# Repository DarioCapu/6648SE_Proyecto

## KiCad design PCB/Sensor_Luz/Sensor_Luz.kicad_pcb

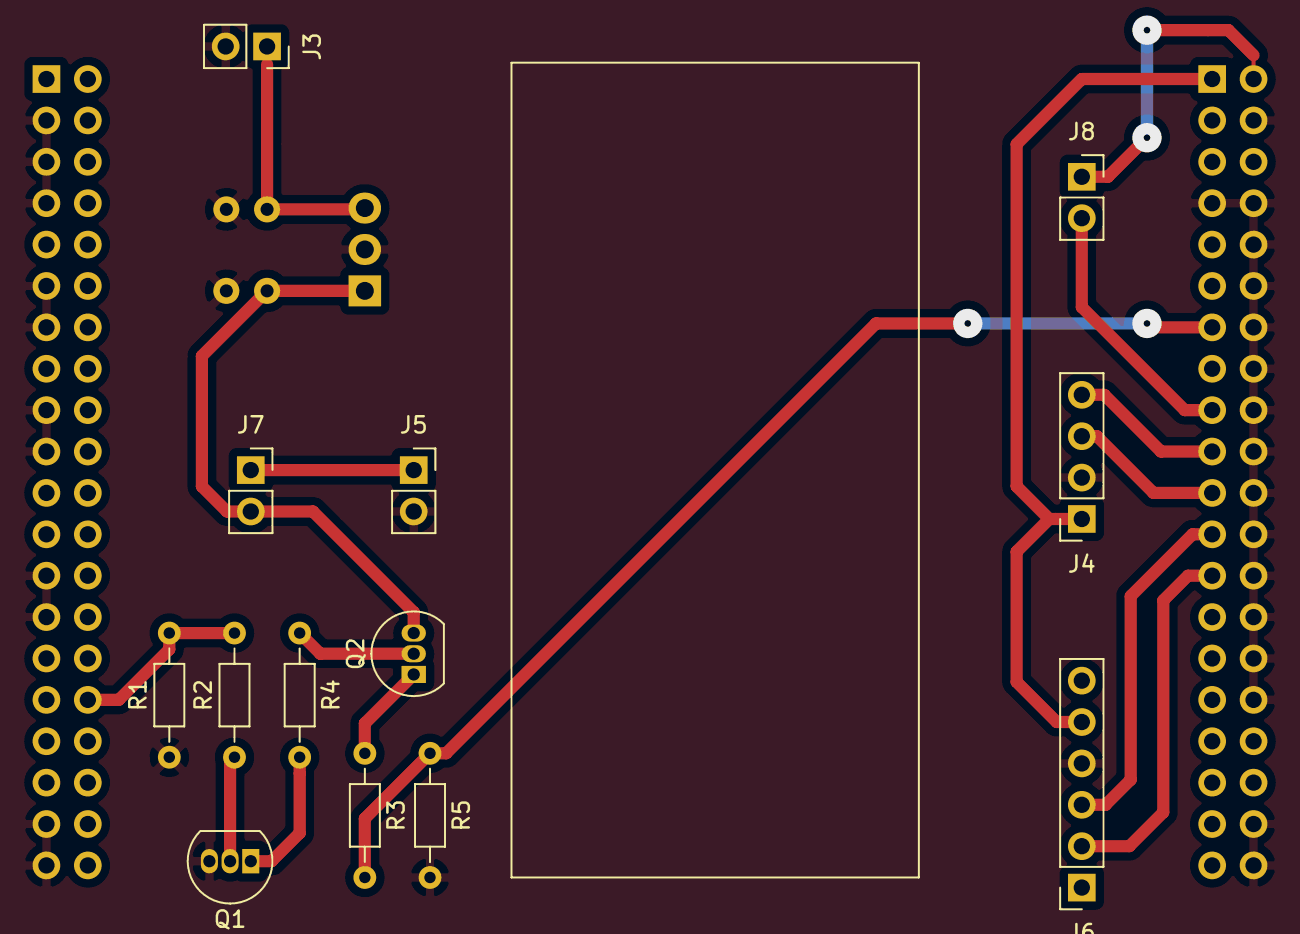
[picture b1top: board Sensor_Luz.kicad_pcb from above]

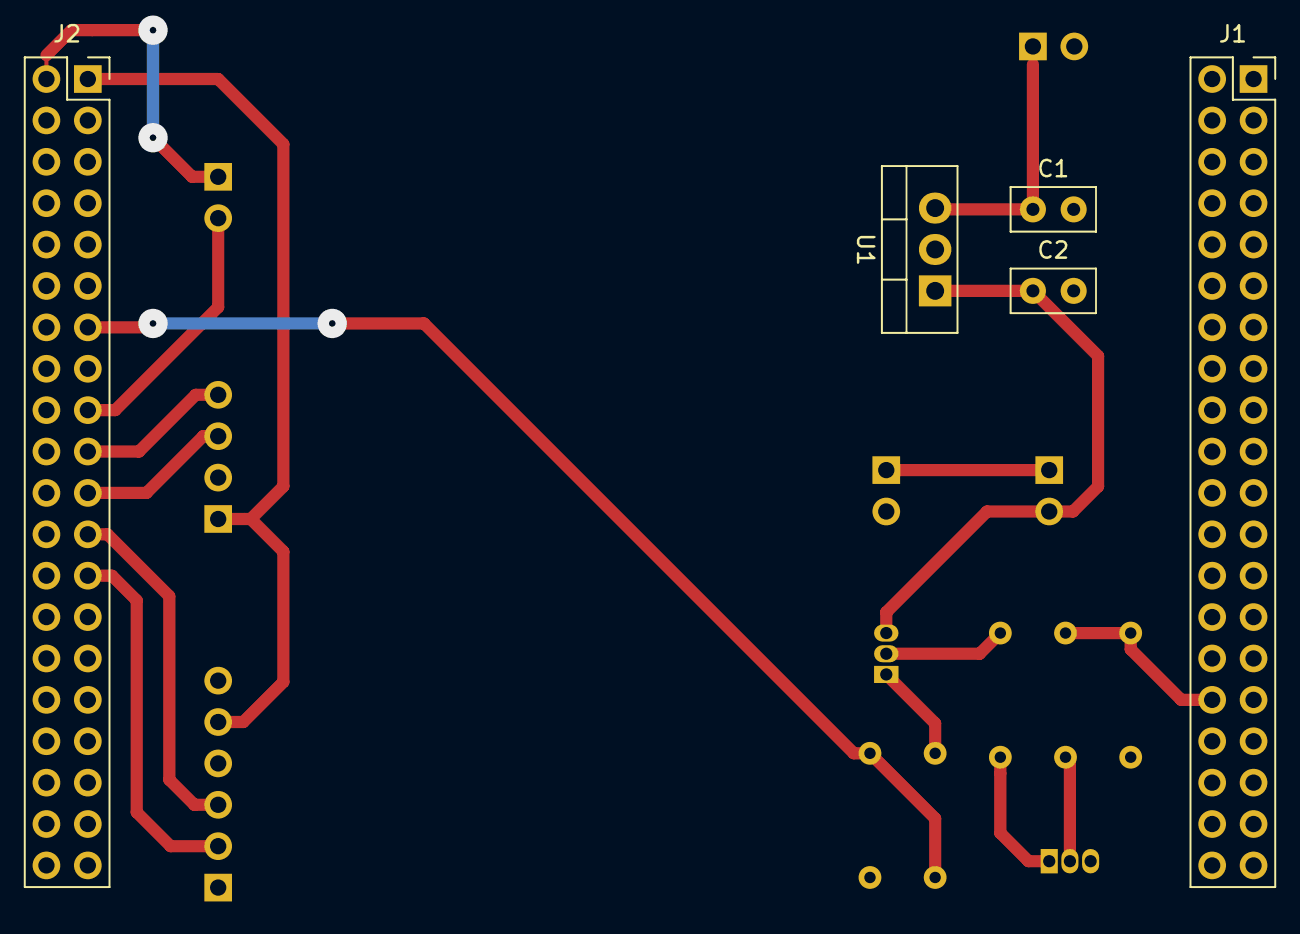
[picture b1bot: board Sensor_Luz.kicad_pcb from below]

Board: 2 copper layers, 18 parts (5 on the bottom side), 17 nets.

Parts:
C1: 0.1uF; C_Disc_D5.0mm_W2.5mm_P2.50mm
C2: 0.33uF; C_Disc_D5.0mm_W2.5mm_P2.50mm
J1, J2: Conn_02x20_Odd_Even; PinSocket_2x20_P2.54mm_Vertical
J3, J5, J7, J8: Conn_01x02_Male; PinSocket_1x02_P2.54mm_Vertical
J4: Conn_01x04_Female; PinSocket_1x04_P2.54mm_Vertical
J6: Conn_01x06_Female; PinSocket_1x06_P2.54mm_Vertical
Q1: BC548; TO-92_Inline
Q2: BC558; TO-92_Inline
R1: 330k; R_Axial_DIN0204_L3.6mm_D1.6mm_P7.62mm_Horizontal
R2: 100k; R_Axial_DIN0204_L3.6mm_D1.6mm_P7.62mm_Horizontal
R3: 47K; R_Axial_DIN0204_L3.6mm_D1.6mm_P7.62mm_Horizontal
R4: 10K; R_Axial_DIN0204_L3.6mm_D1.6mm_P7.62mm_Horizontal
R5: 22k; R_Axial_DIN0204_L3.6mm_D1.6mm_P7.62mm_Horizontal
U1: LM7805_TO220; TO-220-3_Vertical

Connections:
+3V3: J1.1, J2.1, J4.1, J6.5
+5V: J1.2, J2.2, J8.1
+9V: C2.1, J7.2, Q2.3, U1.1
/232_RX: J2.23, J6.3
/232_TX: J2.25, J6.2
/CH1: J2.13, R3.2, R5.1
/GPIO1: J1.32, R1.2, R2.2
/I2C_SCL: J2.21, J4.3
/I2C_SDA: J2.19, J4.4
/VDDA: J2.17, J8.2
GND: C1.2, C2.2, J1.3, J1.5, J1.7, J1.11, J1.13, J1.17, J1.19, J1.25, J1.27, J1.37, J1.39, J2.4, J2.7, J2.8, J2.10, J2.12, J2.14, J2.16, J2.18, J2.20, J2.22, J2.24, J2.26, J2.28, J2.30, J2.32, J2.38, J2.40, J3.2, J4.2, J5.2, J6.4, Q1.3, R1.1, R5.2, U1.2
unnamed: C1.1, J3.1, U1.3
unnamed: J5.1, J7.1
unnamed: Q1.1, R4.2
unnamed: Q1.2, R2.1
unnamed: Q2.1, R3.1
unnamed: Q2.2, R4.1

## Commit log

2019-10-29 Primer commit
2019-11-13 PCB actualizado
2019-11-18 Circuito en spice
2019-11-20 PCB actualizado y hoja de datos
2019-12-01 Cambio PCB
2019-12-05 Cosas nuevas
